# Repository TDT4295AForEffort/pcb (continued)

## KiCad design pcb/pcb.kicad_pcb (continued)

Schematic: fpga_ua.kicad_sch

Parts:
C1101: 100n; C_0805_2012Metric_Pad1.18x1.45mm_HandSolder
C1102, C1103: 47uF; C_1210_3225Metric_Pad1.33x2.70mm_HandSolder
C1104, C1105, C1106, C1107: 4.7uF; C_0805_2012Metric_Pad1.18x1.45mm_HandSolder
C1108, C1109, C1110, C1111, C1112, C1113, C1114, C1115: 470nF; C_0603_1608Metric_Pad1.08x0.95mm_HandSolder
U666: XC7A75T-FTG256; Xilinx_FTG256
Y1101: ECS-2520MV-080-BN-TR; OSC_ECS-2520S25-250-FN-TR

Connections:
+3.3V: C1101.1, C1102.1, C1103.1, C1104.1, C1105.1, C1106.1, C1107.1, C1108.1, C1109.1, C1110.1, C1111.1, C1112.1, C1113.1, C1114.1, C1115.1, U666.A16 (VCCO_15), U666.B13 (VCCO_15), U666.C10 (VCCO_15), U666.E14 (VCCO_15), U666.H15 (VCCO_15), U666.J12 (VCCO_15), U666.L16 (VCCO_14), U666.M13 (VCCO_14), U666.N10 (VCCO_14), U666.P7 (VCCO_14), U666.R14 (VCCO_14), U666.T11 (VCCO_14), Y1101.1 (TRI_STATE), Y1101.4 (VDD); also elsewhere on the board
/fpga/fpga ua/FPGA_GPIO_1: U666.C14 (IO_L8P_T1_AD10P_15)
/fpga/fpga ua/FPGA_GPIO_7: U666.C8 (IO_L1P_T0_AD0P_15)
/fpga/fpga ua/FPGA_GPIO_8: U666.D8 (IO_L6P_T0_15)
/fpga/fpga ua/FPGA_GPIO_9: U666.M12 (IO_L6N_T0_D08_VREF_14)
/fpga/fpga ua/FPGA_GPIO_10: U666.C9 (IO_L1N_T0_AD0N_15)
/fpga/fpga ua/FPGA_GPIO_11: U666.P9 (IO_L18N_T2_A11_D27_14)
FGPA_MCU_EXTRA2: U666.N12 (IO_L13N_T2_MRCC_14); also elsewhere on the board
FPGA_DEBUG_LED_BLOCK14_1: U666.C13 (IO_L12N_T1_MRCC_15); also elsewhere on the board
FPGA_DEBUG_LED_BLOCK15_1: U666.C11 (IO_L11P_T1_SRCC_15); also elsewhere on the board
FPGA_DEBUG_LED_BLOCK35_1: U666.C12 (IO_L11N_T1_SRCC_15); also elsewhere on the board
FPGA_DEBUG_LED_BLOCK35_2: U666.D13 (IO_L12P_T1_MRCC_15); also elsewhere on the board
FPGA_FLASH_D00_IO0: U666.J13 (IO_L1P_T0_D00_MOSI_14); also elsewhere on the board
FPGA_FLASH_D01_IO1: U666.J14 (IO_L1N_T0_D01_DIN_14); also elsewhere on the board
FPGA_FLASH_D02_IO2: U666.K15 (IO_L2P_T0_D02_14); also elsewhere on the board
FPGA_FLASH_D03_IO3: U666.K16 (IO_L2N_T0_D03_14); also elsewhere on the board
FPGA_FLASH_FCSB_CS: U666.L12 (IO_L6P_T0_FCS_B_14); also elsewhere on the board
FPGA_OSCILLATOR_CLOCK: U666.P14 (IO_L12N_T1_MRCC_14), Y1101.3 (OUTPUT)
GND: C1101.2, C1102.2, C1103.2, C1104.2, C1105.2, C1106.2, C1107.2, C1108.2, C1109.2, C1110.2, C1111.2, C1112.2, C1113.2, C1114.2, C1115.2, Y1101.2 (GND); also elsewhere on the board
SRAM_#LB: U666.B15 (IO_L9P_T1_DQS_AD3P_15); also elsewhere on the board
SRAM_#OE: U666.A15 (IO_L9N_T1_DQS_AD3N_15); also elsewhere on the board
SRAM_#UB: U666.B16 (IO_L10N_T1_AD11N_15); also elsewhere on the board
SRAM_#WE: U666.T14 (IO_L10P_T1_D14_14); also elsewhere on the board
SRAM_A0: U666.T15 (IO_L10N_T1_D15_14); also elsewhere on the board
SRAM_A5: U666.B12 (IO_L5P_T0_AD9P_15); also elsewhere on the board
SRAM_A6: U666.A13 (IO_L7P_T1_AD2P_15); also elsewhere on the board
SRAM_A7: U666.A14 (IO_L7N_T1_AD2N_15); also elsewhere on the board
SRAM_A8: U666.H16 (IO_L22P_T3_A17_15); also elsewhere on the board
SRAM_A9: U666.J16 (IO_L23N_T3_FWE_B_15); also elsewhere on the board
SRAM_A10: U666.J15 (IO_L23P_T3_FOE_B_15); also elsewhere on the board
SRAM_A11: U666.L14 (IO_L4P_T0_D04_14); also elsewhere on the board
SRAM_A12: U666.M16 (IO_L7P_T1_D09_14); also elsewhere on the board
SRAM_A13: U666.N16 (IO_L7N_T1_D10_14); also elsewhere on the board
SRAM_A14: U666.M14 (IO_L4N_T0_D05_14); also elsewhere on the board
SRAM_A15: U666.P16 (IO_L8N_T1_D12_14); also elsewhere on the board
SRAM_A16: U666.M15 (IO_L3N_T0_DQS_EMCCLK_14); also elsewhere on the board
SRAM_A17: U666.R16 (IO_L9N_T1_DQS_D13_14); also elsewhere on the board
SRAM_A19: U666.B14 (IO_L8N_T1_AD10N_15); also elsewhere on the board
SRAM_D1: U666.T5 (IO_L23N_T3_A02_D18_14); also elsewhere on the board
SRAM_D2: U666.T7 (IO_L21P_T3_DQS_14); also elsewhere on the board
SRAM_D3: U666.T8 (IO_L21N_T3_DQS_A06_D22_14); also elsewhere on the board
SRAM_D4: U666.T9 (IO_L22P_T3_A05_D21_14); also elsewhere on the board
SRAM_D5: U666.T10 (IO_L22N_T3_A04_D20_14); also elsewhere on the board
SRAM_D6: U666.T12 (IO_L15N_T2_DQS_DOUT_CSO_B_14); also elsewhere on the board
SRAM_D7: U666.T13 (IO_L16N_T2_A15_D31_14); also elsewhere on the board
SRAM_D8: U666.G15 (IO_L24N_T3_RS0_15); also elsewhere on the board
SRAM_D9: U666.G16 (IO_L22N_T3_A16_15); also elsewhere on the board
SRAM_D10: U666.F15 (IO_L18P_T2_A24_15); also elsewhere on the board
SRAM_D11: U666.E15 (IO_L18N_T2_A23_15); also elsewhere on the board
SRAM_D12: U666.E16 (IO_L17P_T2_A26_15); also elsewhere on the board
SRAM_D13: U666.D15 (IO_L15N_T2_DQS_ADV_B_15); also elsewhere on the board
SRAM_D14: U666.D16 (IO_L17N_T2_A25_15); also elsewhere on the board
SRAM_D15: U666.C16 (IO_L10P_T1_AD11P_15); also elsewhere on the board
vga_b1: U666.B10 (IO_L4P_T0_15); also elsewhere on the board
vga_b2: U666.A10 (IO_L3N_T0_DQS_AD1N_15); also elsewhere on the board
vga_b3: U666.B9 (IO_L3P_T0_DQS_AD1P_15); also elsewhere on the board
vga_b4: U666.A9 (IO_L2N_T0_AD8N_15); also elsewhere on the board
vga_b5: U666.A8 (IO_L2P_T0_AD8P_15); also elsewhere on the board
vga_hsync: U666.A12 (IO_L5N_T0_AD9N_15); also elsewhere on the board
vga_vsync: U666.B11 (IO_L4N_T0_15); also elsewhere on the board

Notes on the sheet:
Clock from mcu in case occilator does not work.

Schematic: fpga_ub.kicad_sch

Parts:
C1201: 47uF; C_1210_3225Metric_Pad1.33x2.70mm_HandSolder
C1202, C1203: 4.7uF; C_0805_2012Metric_Pad1.18x1.45mm_HandSolder
C1204, C1205, C1206, C1207: 470nF; C_0603_1608Metric_Pad1.08x0.95mm_HandSolder
J1201: Conn_02x07_Top_Bottom; PinHeader_2x07_P2.54mm_Vertical
U666: XC7A75T-FTG256; Xilinx_FTG256

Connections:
+3.3V: C1201.1, C1202.1, C1203.1, C1204.1, C1205.1, C1206.1, C1207.1, J1201.9, U666.A6 (VCCO_35), U666.B3 (VCCO_35), U666.D7 (VCCO_35), U666.E4 (VCCO_35), U666.F1 (VCCO_35), U666.J2 (VCCO_35); also elsewhere on the board
/fpga/fpga ub/FPGA_GPIO_1: J1201.1, U666.C4 (IO_L12N_T1_MRCC_35)
/fpga/fpga ub/FPGA_GPIO_2: J1201.2, U666.D6 (IO_L6P_T0_35)
/fpga/fpga ub/FPGA_GPIO_3: J1201.3, U666.C3 (IO_L7P_T1_AD6P_35)
/fpga/fpga ub/FPGA_GPIO_4: J1201.4, U666.D4 (IO_L12P_T1_MRCC_35)
/fpga/fpga ub/FPGA_GPIO_5: J1201.5, U666.C2 (IO_L7N_T1_AD6N_35)
/fpga/fpga ub/FPGA_GPIO_6: J1201.6, U666.D3 (IO_L11N_T1_SRCC_35)
/fpga/fpga ub/FPGA_GPIO_7: J1201.7, U666.D1 (IO_L10N_T1_AD15N_35)
/fpga/fpga ub/FPGA_GPIO_8: J1201.8, U666.C1 (IO_L9P_T1_DQS_AD7P_35)
FGPA_MCU_EXTRA1: U666.F2 (IO_L15P_T2_DQS_35); also elsewhere on the board
FGPA_MCU_SPI_CLK: U666.H2 (IO_L20P_T3_35); also elsewhere on the board
FGPA_MCU_SPI_CS: U666.G1 (IO_L17N_T2_35); also elsewhere on the board
FGPA_MCU_SPI_SDI: U666.G2 (IO_L17P_T2_35); also elsewhere on the board
FGPA_MCU_SPI_SDO: U666.H1 (IO_L20N_T3_35); also elsewhere on the board
GND: C1201.2, C1202.2, C1203.2, C1204.2, C1205.2, C1206.2, C1207.2, J1201.10, U666.M3 (VCCO_34), U666.R4 (VCCO_34), U666.T1 (VCCO_34); also elsewhere on the board
SRAM_#CE: U666.T3 (IO_L9N_T1_DQS_34); also elsewhere on the board
SRAM_A1: U666.R1 (IO_L7N_T1_34); also elsewhere on the board
SRAM_A2: U666.P1 (IO_L4N_T0_34); also elsewhere on the board
SRAM_A3: U666.N1 (IO_L4P_T0_34); also elsewhere on the board
SRAM_A4: U666.M1 (IO_L2N_T0_34); also elsewhere on the board
SRAM_A18: U666.T2 (IO_L8N_T1_34); also elsewhere on the board
SRAM_D0: U666.T4 (IO_L9P_T1_DQS_34); also elsewhere on the board
vga_g1: U666.B7 (IO_L1P_T0_AD4P_35); also elsewhere on the board
vga_g2: U666.A7 (IO_L1N_T0_AD4N_35); also elsewhere on the board
vga_g3: U666.B6 (IO_L2P_T0_AD12P_35); also elsewhere on the board
vga_g4: U666.B5 (IO_L2N_T0_AD12N_35); also elsewhere on the board
vga_g5: U666.A5 (IO_L3P_T0_DQS_AD5P_35); also elsewhere on the board
vga_g6: U666.B4 (IO_L4P_T0_35); also elsewhere on the board
vga_r1: U666.B1 (IO_L9N_T1_DQS_AD7N_35); also elsewhere on the board
vga_r2: U666.A2 (IO_L8N_T1_AD14N_35); also elsewhere on the board
vga_r3: U666.B2 (IO_L8P_T1_AD14P_35); also elsewhere on the board
vga_r4: U666.A3 (IO_L4N_T0_35); also elsewhere on the board
vga_r5: U666.A4 (IO_L3N_T0_DQS_AD5N_35); also elsewhere on the board

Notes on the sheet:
NOTE: H5 and J5 match devboard LEDS in the default constraints file nonono
FPGA GPIO PINS
flyttet spi pin fra e6 til b4

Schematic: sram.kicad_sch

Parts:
C701, C702: 100n; C_0805_2012Metric_Pad1.18x1.45mm_HandSolder
U701: AS7C316098A-10TIN

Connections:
+3.3V: C701.2, C702.2, U701.12 (VCC), U701.36 (VCC); also elsewhere on the board
GND: C701.1, C702.1, U701.13 (VSS), U701.37 (VSS); also elsewhere on the board
SRAM_#CE: U701.7 (*CE); also elsewhere on the board
SRAM_#LB: U701.42 (*LB); also elsewhere on the board
SRAM_#OE: U701.44 (*OE); also elsewhere on the board
SRAM_#UB: U701.43 (*UB); also elsewhere on the board
SRAM_#WE: U701.18 (*WE); also elsewhere on the board
SRAM_A0: U701.20 (A18); also elsewhere on the board
SRAM_A1: U701.4 (A1); also elsewhere on the board
SRAM_A2: U701.3 (A2); also elsewhere on the board
SRAM_A3: U701.2 (A3); also elsewhere on the board
SRAM_A4: U701.1 (A4); also elsewhere on the board
SRAM_A5: U701.48 (A5); also elsewhere on the board
SRAM_A6: U701.47 (A6); also elsewhere on the board
SRAM_A7: U701.46 (A7); also elsewhere on the board
SRAM_A8: U701.30 (A8); also elsewhere on the board
SRAM_A9: U701.29 (A9); also elsewhere on the board
SRAM_A10: U701.28 (A10); also elsewhere on the board
SRAM_A11: U701.27 (A11); also elsewhere on the board
SRAM_A12: U701.24 (A14); also elsewhere on the board
SRAM_A13: U701.23 (A15); also elsewhere on the board
SRAM_A14: U701.26 (A12); also elsewhere on the board
SRAM_A15: U701.22 (A16); also elsewhere on the board
SRAM_A16: U701.25 (A13); also elsewhere on the board
SRAM_A17: U701.21 (A17); also elsewhere on the board
SRAM_A18: U701.5 (A0); also elsewhere on the board
SRAM_A19: U701.45 (A19); also elsewhere on the board
SRAM_D0: U701.8 (DQ0); also elsewhere on the board
SRAM_D1: U701.9 (DQ1); also elsewhere on the board
SRAM_D2: U701.10 (DQ2); also elsewhere on the board
SRAM_D3: U701.11 (DQ3); also elsewhere on the board
SRAM_D4: U701.14 (DQ4); also elsewhere on the board
SRAM_D5: U701.15 (DQ5); also elsewhere on the board
SRAM_D6: U701.16 (DQ6); also elsewhere on the board
SRAM_D7: U701.17 (DQ7); also elsewhere on the board
SRAM_D8: U701.32 (DQ8); also elsewhere on the board
SRAM_D9: U701.33 (DQ9); also elsewhere on the board
SRAM_D10: U701.34 (DQ10); also elsewhere on the board
SRAM_D11: U701.35 (DQ11); also elsewhere on the board
SRAM_D12: U701.38 (DQ12); also elsewhere on the board
SRAM_D13: U701.39 (DQ13); also elsewhere on the board
SRAM_D14: U701.40 (DQ14); also elsewhere on the board
SRAM_D15: U701.41 (DQ15); also elsewhere on the board

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
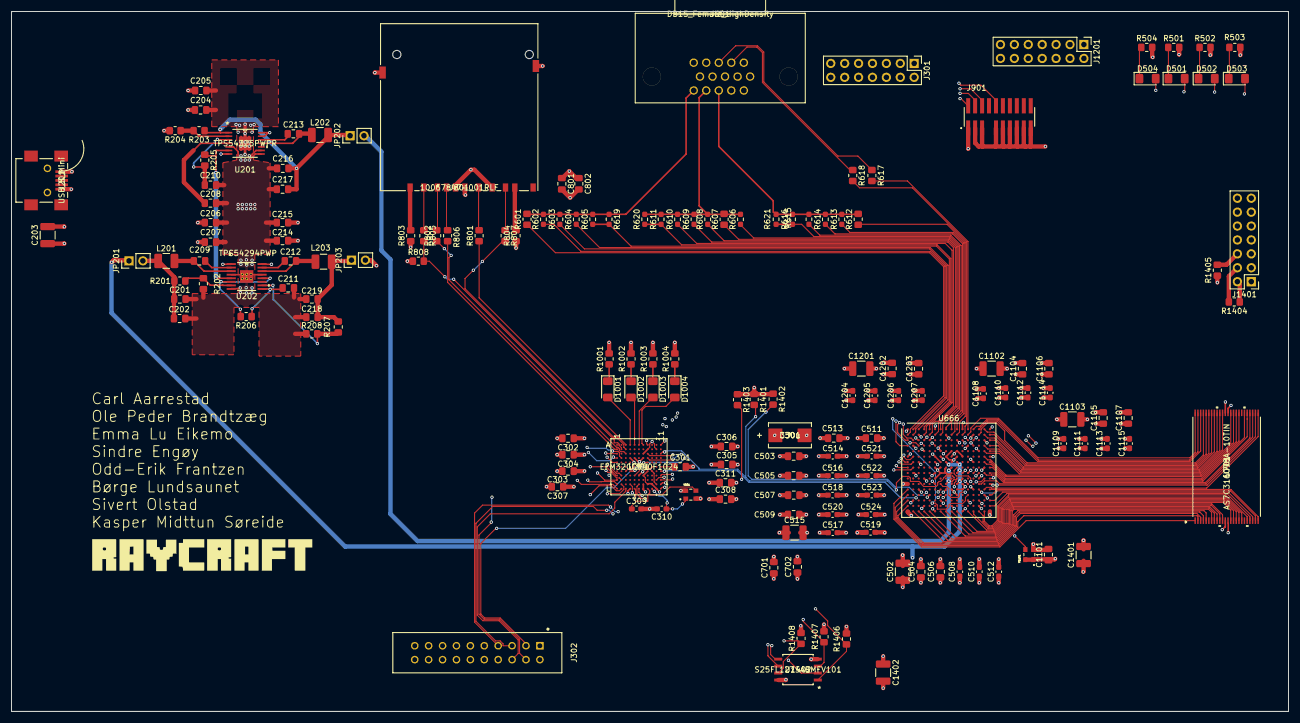
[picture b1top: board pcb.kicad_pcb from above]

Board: 6 copper layers, 233.3 x 127.9 mm, 165 parts (0 on the bottom side), 166 nets.

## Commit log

2022-09-14 add some components
2022-09-14 begin work on pcb
2022-09-14 oops
2022-09-14 add mcu sheet with finished debug connector
2022-09-14 add symbol libraries for mcu
2022-09-14 more work on psu
2022-09-16 more mcu
2022-09-16 add mcu_bak file
2022-09-16 finish wiring
2022-09-16 add relative path to symbols
2022-09-16 add global labels and footprint
2022-09-16 finish psu(maybe???)
2022-09-17 add component values
2022-09-17 io_controller_inputs on mcu
2022-09-17 finish onboard controller
2022-09-17 begin adding fpga
2022-09-17 add flash memory component for fpga
2022-09-17 oops I think I updated these
2022-09-17 add externall controller
2022-09-17 kicad said I needed to save
2022-09-17 add spi pins and finish onboard_controller
2022-09-18 finish mcu :-)
2022-09-18 add jtag connector and flash to fpga
2022-09-19 fpga shite
2022-09-19 add vga
2022-09-19 added new_vga and sram
2022-09-20 connect sram and vga to fpga
2022-09-20 add capasitor values
2022-09-20 add capasitro values again
2022-09-22 add missing values again
2022-09-22 commit before merge
2022-09-27 maybe finished schematic
2022-09-28 everything except crystal
2022-09-29 add oscilattor + spi debug+ cap on sramd
2022-09-29 add footprints
2022-09-29 add footprints + fix unnconnected
2022-09-30 start layout
2022-09-30 connect onboard controller
2022-10-01 fix nasty shorts
2022-10-01 more traces
2022-10-01 add power input
2022-10-01 change footprint of connector
2022-10-01 add pcb file oops
2022-10-01 fuckeru
2022-10-01 add footprint to usb
2022-10-01 change footprint of debug_connector
2022-10-01 switch some pins for more erqonomiq layout
2022-10-01 add/fix sd,usb,flash footprints
2022-10-01 assign the last footprints
2022-10-01 forgot to add sd card symbol
2022-10-02 workon
2022-10-02 fix vga resistors
2022-10-02 fix joystick
2022-10-02 deconect shield on joystick
2022-10-02 psu wiring and power cables
2022-10-02 add correct vga resistors
2022-10-02 change location of stram pin
2022-10-02 make lines between sram and fpga
2022-10-02 move capasitor
2022-10-02 add 1.0v and 1.8v decoupling for fpga, clean capacitors
2022-10-02 vga is live
2022-10-03 decouple fpga, clean up a bit
2022-10-03 is donegst
2022-10-03 fix capacitor values and footprints
2022-10-03 fix edge + fills
2022-10-03 creeper? aw man
2022-10-03 fix some schematic erc errors
2022-10-03 replace jumpers with pin headers
2022-10-03 fix new vga
2022-10-03 logo
2022-10-04 fix errors in schematic
2022-10-04 up via size, going to remove onboard-controller
2022-10-04 fix vias
2022-10-04 fix psu
2022-10-04 is donegit !
2022-10-04 sike
2022-10-04 cleanup vias etc
